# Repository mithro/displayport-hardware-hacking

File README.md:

View this project on [CADLAB.io](https://cadlab.io/project/2210). 

This repository contains schematics for working with DisplayPort.

Currently there are three sub-projects;

 * dp-aux-intercept - A board for connecting DisplayPort AUX signals to FPGA
   boards for interception and manipulation.

 * dp-to-pcie - An adapter board for allowing FPGA development boards with
   PCI-Express 4x interfaces to be instead used with DisplayPort.

 * dp-to-hsmc - An expansion board for the Altera HSMC standard supporting up
   to two DisplayPort sinks and two DisplayPort sources.

These works are released under the 
[Creative Commons Attribution-ShareAlike 4.0 International License (CC BY-SA 4.0)](http://creativecommons.org/licenses/by-sa/4.0/)

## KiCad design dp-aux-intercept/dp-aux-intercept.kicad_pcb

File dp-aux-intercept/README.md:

This schematic is design to allow FPGA development boards to intercept and
manipulate the auxiliary signals (plus hotplug and config signals) between a
display port source (such as a computer) and a display port sink (such as a
display). The high speed data lanes are connected directly between the source
and sink and not accessible.

The AUX signal is bi-directional, half duplex LVDS signal which operates at
~1.2 Megabit/s on older DisplayPort versions and ~720 Megabit/s in the later
specifications. It carries information device management and control data such
as EDID and DPMS standards. In theory it could also carry a USB signal.

# Board Manufacturing

 *  5mil (0.127mm) trace width
 *  5mil (0.127mm) trace clearance

 * 12 mil (0.3048mm) drill size
 *  6 mil (0.1524mm) annular ring
 * 24 mil (0.6096mm) via size (6mil+12mil+6mil)

 *  6 mil (0.1524) silkscreen width

This can be meet by;
 * [Hackvana by requesting the 5mil option](https://docs.google.com/document/d/1p6FH25ltGpzJQ5_8fbflDukqEKghiEcpuhJpngth2Is/edit)
 * [OHS Park's Four Layer Boards](http://docs.oshpark.com/services/)

# Board connectors
 
The board breaks out the AUX signals onto two Diligent PMOD compatible headers.
The JAUX jumpers select which PMOD header is currently in use.

## PAUX1 Mode

The first PMOD header labeled PAUX1 is designed to be used by devices which
support switching the direction of their I/O pins quickly enough. It maps both
AUX pairs and the HPD (hot plug) signal into a single PMOD connector. FPGAs
compatible with this are;

 * Spartan 6 when using the DISPLAY_PORT I/O standard (which only supports the
   1.2 Megabit/s mode).

 * Xilinx Series 7 FPGAs such as the Atrix, Zynq or Virtex-7 devices.

PAUX1 should be connected to the FPGA;

 * Pin 1 - AUX+ signal on computer side, configure 2.5V compatible
   bi-directional LVDS.
 * Pin 3 - AUX- signal on computer side, configure 2.5V compatible
   bi-directional LVDS.
 * Pin 5 is NC.
 * Pin 7 - HPD on computer side, configure 3.3V compatible LVCMOS33 output.

 * Pin 2 - AUX+ signal on display side, configure 2.5V compatible
   bi-directional LVDS.
 * Pin 4 - AUX- signal on display side, configure 2.5V compatible
   bi-directional LVDS.
 * Pin 6 is NC.
 * Pin 8 - HPD on display side, configure 3.3V compatible LVCMOS33 input.

 * Pin 9 and Pin 10 - 3.3V - VCC
 * Pin 11 and Pin 12 - GND

When using PAUX1 the board should be configured as follows;

 * All the JAUX jumpers are set to the "1" side (jumping Pin 1 and Pin 2
   together).

 * On PCFG1, Pins 5 and Pin 6 should **not be** connected.
   (**Dis**connecting the HPD signal from computer to display, allowing the
    FPGA to control the HPD signal.)

 * On J**C**CFG1, Pins 5 and Pin 6 should **be** connected.
   (Pulling the HPD signal on the **c**omputer side down.)

 * On J**D**CFG1, Pins 5 and Pin 6 should **be** connected.
   (Pulling the HPD signal on the **d**isplay side down.)

## PAUX2 Mode

The second PMOD header labeled PAUX2 is designed to be used by devices which
need to use two pairs of LVDS pins connected to each AUX lines. (When using
PAUX2 a second PMOD header the only way to receive the HPD is to use the PCFG1
header.) FPGAs compatible with this header are;

 * Spartan 6 when using the LVDS I/O standard.

To use PAUX2, you must always make sure the board has the following configured;

 * All the JAUX jumpers are set to the "2" side (jumping Pin 2 and Pin 3
   together).

PAUX2 should be connected to the FPGA in the following way;

 * Pin 1 - AUX+ signal on computer side, configure 2.5V compatible
   **output** LVDS.
 * Pin 3 - AUX- signal on computer side, configure 2.5V compatible
   **output** LVDS.

 * Pin 5 - AUX+ signal on computer side, configure 2.5V compatible
   **input** LVDS.
 * Pin 7 - AUX- signal on computer side, configure 2.5V compatible
   **input** LVDS.

 * Pin 2 - AUX+ signal on display side, configure 2.5V compatible
   **output** LVDS.
 * Pin 4 - AUX- signal on display side, configure 2.5V compatible
   **output** LVDS.

 * Pin 6 - AUX+ signal on display side, configure 2.5V compatible
   **input** LVDS.
 * Pin 8 - AUX- signal on display side, configure 2.5V compatible
   **input** LVDS.

 * Pin 9 and Pin 10 - 3.3V - VCC
 * Pin 11 and Pin 12 - GND

When using PAUX2 the board should be configured in one of two ways. 

If access to the HPD is **needed** follow the instructions for **using** the
PCFG1 expanded signals connector.

If access to the HPD is **not needed**;

 * On PCFG1, Pins 5 and Pin 6 should **be** connected. 
   (Connecting the HPD signal from computer to display.)

 * On J**C**CFG1, Pins 5 and Pin 6 should **not be** connected.
   (Leaving the HPD signal on the **c**omputer side floating.)

 * On J**D**CFG1, Pins 5 and Pin 6 should **not be** connected.
   (Leaving the HPD signal on the **d**isplay side floating.)

## PCFG1 - Expanded signals

The PCFG1 is also a PMOD compatible header but is found in male form to allow
it to also be used with jumpers. This header provides access to the CONFIG
lines (used with DP++ signaling) and alternative access to the HPD signal when
using PAUX2 mode.

#### Not using extended signals

When **not using** PCFG1, the board should be configured as follows;

 * On PCFG1;
   * Pin 1 and Pin 2 should **be** connected. 
     (Connecting CONFIG1 directly from the computer to the display.)

   * Pin 3 and Pin 4 should **be** connected.
     (Connecting CONFIG2 directly from the computer to the display.)

   * Pin 5 and Pin 6 should be configured as described in either PAUX1 or PAUX2
     section.

 * On J**C**CFG1,
   * Pins 1 and Pin 2 should **not be** connected.
     (Leaving the CONFIG1 signal on the **c**omputer side floating.)

   * Pins 3 and Pin 4 should **not be** connected.
     (Leaving the CONFIG2 signal on the **c**omputer side floating.)

   * Pin 5 and Pin 6 should be configured as described in either PAUX1 or PAUX2
     section.

 * On J**D**CFG1,
   * Pins 1 and Pin 2 should **not be** connected.
     (Leaving the CONFIG1 signal on the **d**isplay side floating.)

   * Pins 3 and Pin 4 should **not be** connected.
     (Leaving the CONFIG2 signal on the **d**isplay side floating.)

   * Pin 5 and Pin 7 should be configured as described in either PAUX1 or PAUX2
     section.

#### Using extended signals

PCFG1 should be connected to your FPGA.

 * Pin 1 - CONFIG1 on computer side, configure 3.3V compatible LVCMOS33
   ?input?.
 * Pin 3 - CONFIG2 on computer side, configure 3.3V compatible LVCMOS33
   ?input?.
 * Pin 5 - HPD on computer side, configure 3.3V compatible LVCMOS33 output.

 * Pin 2 - CONFIG1 on display side, configure 3.3V compatible LVCMOS33 ?input?.
 * Pin 4 - CONFIG2 on display side, configure 3.3V compatible LVCMOS33 ?input?.
 * Pin 6 - HPD on display side, configure 3.3V compatible LVCMOS33 input.

When **using** PCFG1, the board should be configured as follows;

 * On J**C**CFG1,
   * Pins 1 and Pin 2 should **be** connected.
     (Leaving the CONFIG1 signal on the **c**omputer side floating.)

   * Pins 3 and Pin 4 should **not be** connected.
     (Leaving the CONFIG2 signal on the **c**omputer side floating.)

   * Pin 4 and Pin 5 should be configured as described in either PAUX1 or PAUX2
     section.

 * On J**D**CFG1,
   * Pins 1 and Pin 2 should **not be** connected.
     (Leaving the CONFIG1 signal on the **d**isplay side floating.)

   * Pins 3 and Pin 4 should **not be** connected.
     (Leaving the CONFIG2 signal on the **d**isplay side floating.)

   * Pin 4 and Pin 5 should be configured as described in either PAUX1 or PAUX2
     section.

 * PCFG1 should be connected to the FPGA. Pins 5 and Pin 6 will provide the HPD
   signals.

 * On J**C**CFG1, Pins 5 and Pin 6 should **be** connected.
   (Pulling the HPD signal on the **c**omputer side down.)

 * On J**D**CFG1, Pins 5 and Pin 6 should **be** connected.
   (Pulling the HPD signal on the **d**isplay side down.)

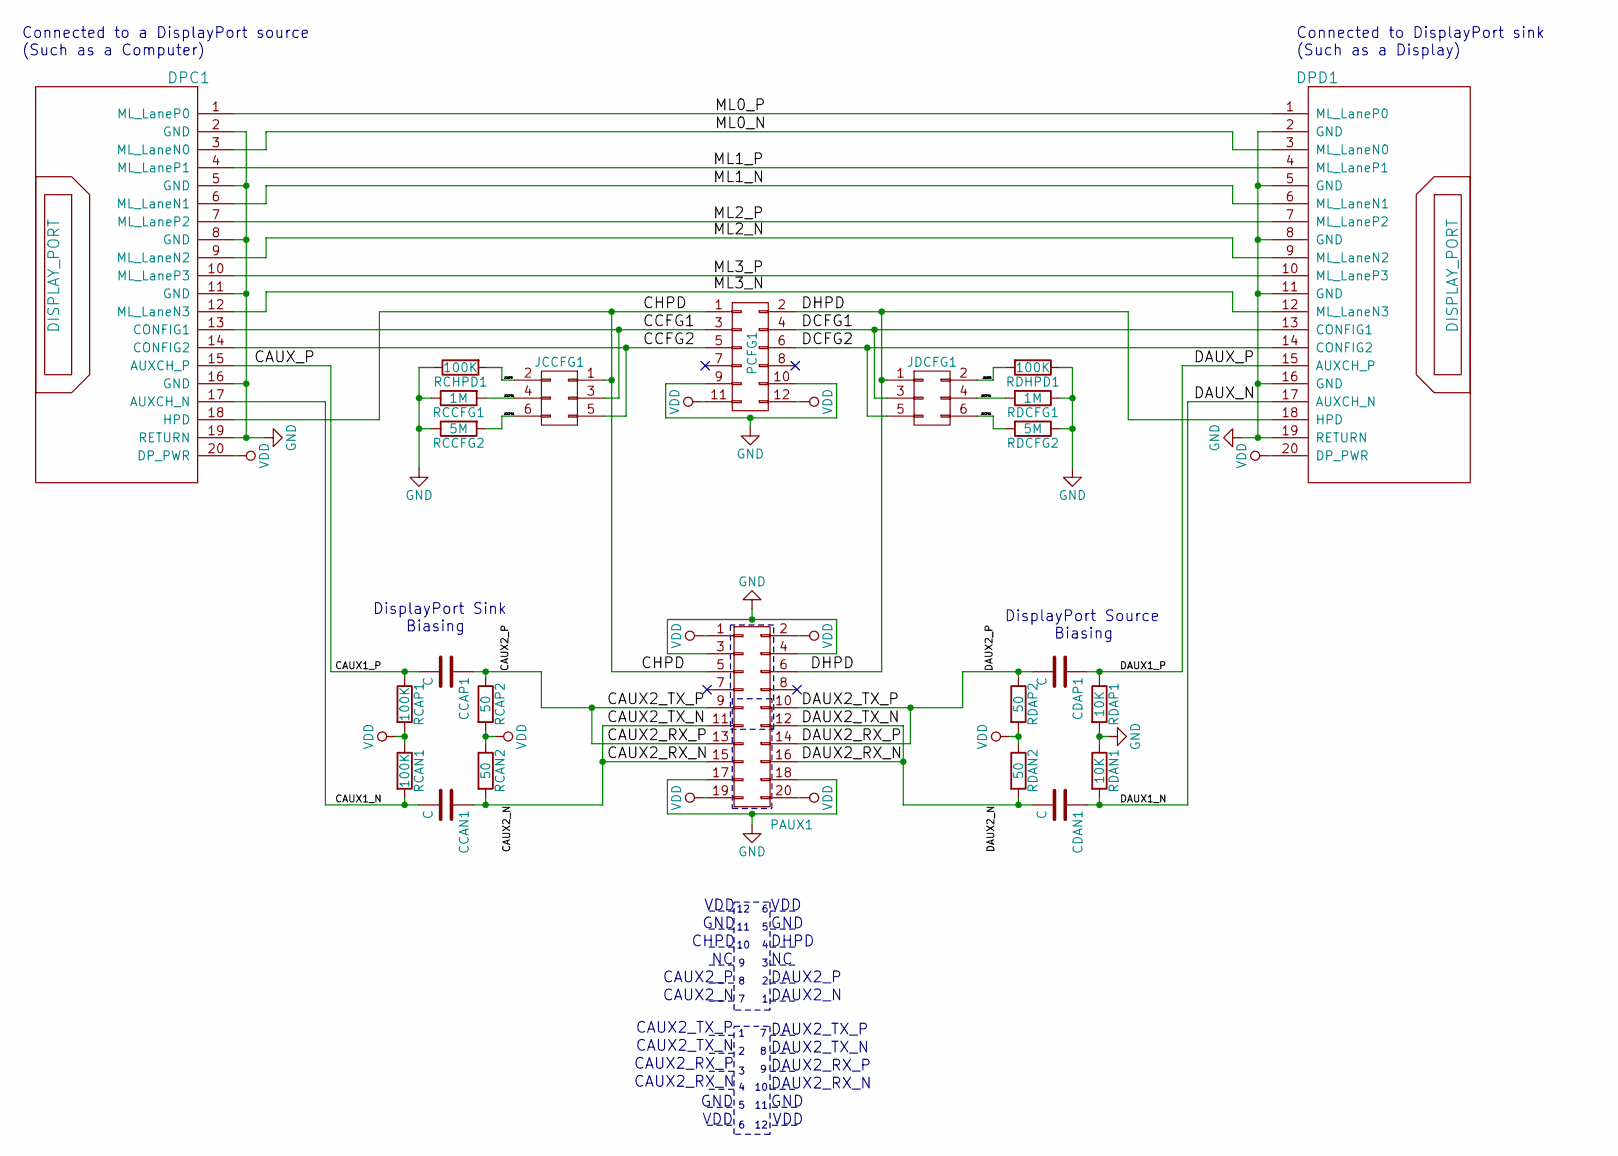
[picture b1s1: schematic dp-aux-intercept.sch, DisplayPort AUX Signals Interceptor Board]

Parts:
CCAN1: C; C_0805_HandSoldering
CCAP1: C; C_0805_HandSoldering
CDAN1: C; C_0805_HandSoldering
CDAP1: C; C_0805_HandSoldering
DPC1: DISPLAY_PORT; 2040210-1
DPD1: DISPLAY_PORT; 2040210-1
JCCFG1: CONN_02X03; Pin_Header_Straight_2x03
JDCFG1: CONN_02X03; Pin_Header_Straight_2x03
PAUX1: CONN_02X10; Socket_Strip_Angled_2x10
PCFG1: CONN_02X06; Pin_Header_Straight_2x06
RCAN1: 100K; R_0603_HandSoldering
RCAN2: 50; R_0603_HandSoldering
RCAP1: 100K; R_0603_HandSoldering
RCAP2: 50; R_0603_HandSoldering
RCCFG1: 1M; R_0603_HandSoldering
RCCFG2: 5M; R_0603_HandSoldering
RCHPD1: 100K; R_0603_HandSoldering
RDAN1: 10K; R_0603_HandSoldering
RDAN2: 50; R_0603_HandSoldering
RDAP1: 10K; R_0603_HandSoldering
RDAP2: 50; R_0603_HandSoldering
RDCFG1: 1M; R_0603_HandSoldering
RDCFG2: 5M; R_0603_HandSoldering
RDHPD1: 100K; R_0603_HandSoldering

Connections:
/CAUX1_N: CCAN1.2, DPC1.17 (AUXCH_N), RCAN1.2
/CAUX1_P: CCAP1.2, DPC1.15 (AUXCH_P), RCAP1.1
/CAUX2_N: CCAN1.1, PAUX1.11, PAUX1.15, RCAN2.2
/CAUX2_P: CCAP1.1, PAUX1.9, PAUX1.13, RCAP2.1
/CCFG1: DPC1.13 (CONFIG1), JCCFG1.3, PCFG1.3
/CCFG2: DPC1.14 (CONFIG2), JCCFG1.5, PCFG1.5
/CHPD: DPC1.18 (HPD), JCCFG1.1, PAUX1.5, PCFG1.1
/DAUX1_N: CDAN1.1, DPD1.17 (AUXCH_N), RDAN1.2
/DAUX1_P: CDAP1.1, DPD1.15 (AUXCH_P), RDAP1.1
/DAUX2_N: CDAN1.2, PAUX1.12, PAUX1.16, RDAN2.2
/DAUX2_P: CDAP1.2, PAUX1.10, PAUX1.14, RDAP2.1
/DCFG1: DPD1.13 (CONFIG1), JDCFG1.3, PCFG1.4
/DCFG2: DPD1.14 (CONFIG2), JDCFG1.5, PCFG1.6
/DHPD: DPD1.18 (HPD), JDCFG1.1, PAUX1.6, PCFG1.2
/JCCFG1: JCCFG1.4, RCCFG1.2
/JCCFG2: JCCFG1.6, RCCFG2.2
/JCHPD: JCCFG1.2, RCHPD1.2
/JDCFG1: JDCFG1.4, RDCFG1.2
/JDCFG2: JDCFG1.6, RDCFG2.2
/JDHPD: JDCFG1.2, RDHPD1.2
/ML0_N: DPC1.3 (ML_LaneN0), DPD1.3 (ML_LaneN0)
/ML0_P: DPC1.1 (ML_LaneP0), DPD1.1 (ML_LaneP0)
/ML1_N: DPC1.6 (ML_LaneN1), DPD1.6 (ML_LaneN1)
/ML1_P: DPC1.4 (ML_LaneP1), DPD1.4 (ML_LaneP1)
/ML2_N: DPC1.9 (ML_LaneN2), DPD1.9 (ML_LaneN2)
/ML2_P: DPC1.7 (ML_LaneP2), DPD1.7 (ML_LaneP2)
/ML3_N: DPC1.12 (ML_LaneN3), DPD1.12 (ML_LaneN3)
/ML3_P: DPC1.10 (ML_LaneP3), DPD1.10 (ML_LaneP3)
GND: DPC1.2 (GND), DPC1.5 (GND), DPC1.8 (GND), DPC1.11 (GND), DPC1.16 (GND), DPC1.19 (RETURN), DPD1.2 (GND), DPD1.5 (GND), DPD1.8 (GND), DPD1.11 (GND), DPD1.16 (GND), DPD1.19 (RETURN), PAUX1.3, PAUX1.4, PAUX1.17, PAUX1.18, PCFG1.9, PCFG1.10, RCCFG1.1, RCCFG2.1, RCHPD1.1, RDAN1.1, RDAP1.2, RDCFG1.1, RDCFG2.1, RDHPD1.1
VDD: DPC1.20 (DP_PWR), DPD1.20 (DP_PWR), PAUX1.1, PAUX1.2, PAUX1.19, PAUX1.20, PCFG1.11, PCFG1.12, RCAN1.1, RCAN2.1, RCAP1.2, RCAP2.2, RDAN2.1, RDAP2.2

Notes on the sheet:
DisplayPort Sink Biasing
Connected to a DisplayPort source (Such as a Computer)
Connected to DisplayPort sink (Such as a Display)
DisplayPort Source Biasing
VDD
GND
CHPD
DHPD
DAUX2_P
DAUX2_N
CAUX2_P
CAUX2_N
DAUX2_TX_P
DAUX2_TX_N
CAUX2_TX_P
CAUX2_TX_N
DAUX2_RX_P
DAUX2_RX_N
CAUX2_RX_P
CAUX2_RX_N

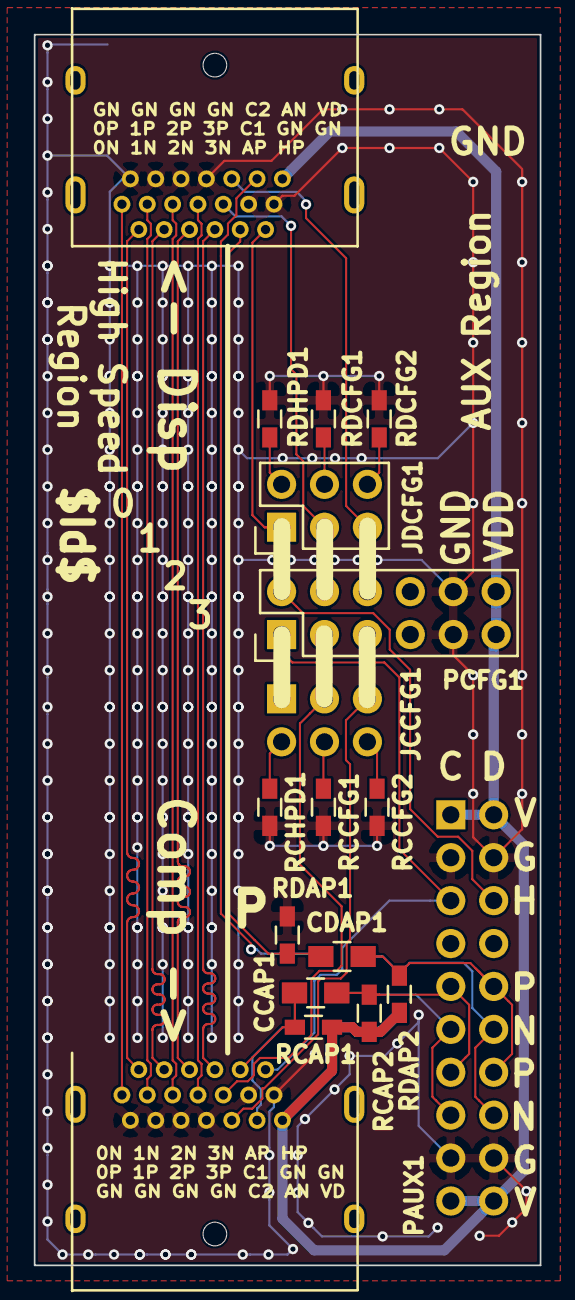
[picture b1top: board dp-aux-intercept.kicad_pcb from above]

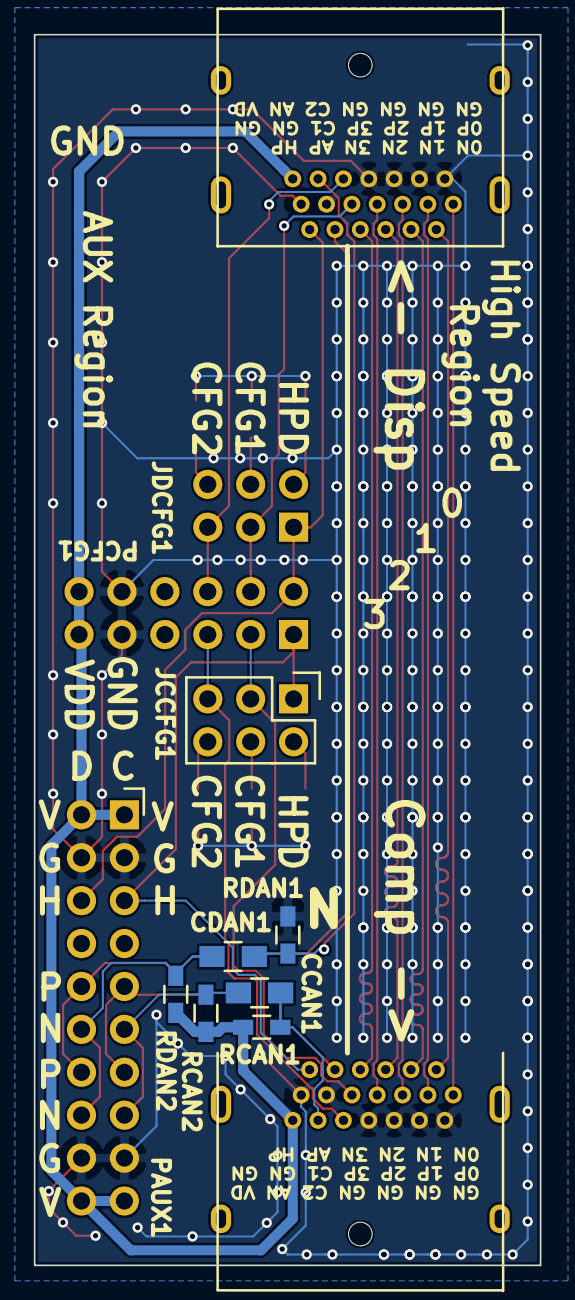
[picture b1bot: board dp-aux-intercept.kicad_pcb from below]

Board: 4 copper layers, 29.9 x 72.9 mm, 24 parts (9 on the bottom side), 30 nets.

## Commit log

2015-06-13 Adding DisplayPort and PCIe connectors.
2015-06-13 Initial empty schematic and project.
2015-06-13 Adding initial schematic for the interceptor.
2015-06-13 Adding initial README and license file.
2015-06-13 Adding .gitignore file.
2015-06-13 Updates to the dp-to-pcie schematic.
2015-06-13 Updating the comments in the schematic.
2015-06-13 Initial empty schematic.
2015-06-13 Initial scatter.
2015-06-13 More backup files..
2015-06-13 Work on the PCB.
2015-06-13 Rename the display port part to match component name.
2015-06-13 Adding through hole DisplayPort component.
2015-06-13 Update library information.
2015-06-13 Adding newline to README.md
2015-06-13 Adding a README file for the dp-to-pcie schematic.
2015-06-13 Adding a README for the HSMC to DisplayPort project.
2015-06-13 Adding schematic description.
2015-06-13 Adding more descriptions.
2015-06-15 Adding some extra info about the HSMC stuff.
2015-06-15 Add DisplayPort footprint.
2015-06-15 Adding part from @brightcloudy
2015-06-15 Changing to using the through-hole DisplayPort connectors.
2015-06-15 Importing the updated netlist.
2015-06-15 Changing the PAUX1 and PAUX2 to be right angle connectors.
2015-06-15 Assigning footprints to AUX select headers.
2015-06-15 Temp commit.
2015-06-15 Adding silkscreen to both sides.
2015-06-15 Lots of updates to the PCB.
2015-06-16 Alternative method of two PMOD styles.
2015-06-16 Enough routing for tonight.
2015-06-17 Information about the Xilinx KC705 board.
2015-06-17 Add QTH-0909-01-L-D-A footprint.
2015-06-17 Added schematic part for QTH-090-01-L-D-A.
2015-06-19 Start of the dp-to-hsmc stuff.
2015-06-19 Adding the HSMC part from @brightcloudy
2015-06-19 Updated QTH-090-01-L-D-A pinout to comply with HSMC pinout. Created HSMC-SE.lib for HSMC Standard Single-Ended pin assignment.
2015-06-19 Add HSMC Standard Differential Configuration schematic part.
2015-06-19 Add mounting holes in the QTH-090-01-L-D-A footprint.
2015-06-28 PCB routing temp commit.
2015-06-28 Adding a .keepme file.
2015-06-28 Moving around in preparation for merging.
2015-06-28 Adding pin information CSV files.
2015-06-28 Adding link to spreadsheet with further info.
2015-06-28 Small fixes.
2015-06-28 Reordering headers to make routing easier.
2015-06-28 More temp commit.
2016-06-24 Finishing connecting the traces.
2016-06-24 Converting mm to mil.
    * 0.125mm -> 5mil (0.1270mm)
    * 0.150mm -> 6mil (0.1524mm)
2016-06-24 Converting to 5mil/5mil + Documenting the DRC requested.
2016-06-24 Small connectivity fix.
2016-06-24 Fixing the vias
2016-06-24 Adding ground plane and tie vias
2016-06-24 Lots of work.
    * Fixing the GND tie vias.
    * Working on the silkscreen.
2016-06-24 Working on the silk screen.
2016-07-03 Fixing the hackvana link.
2016-08-01 Improving the silk screen.
2016-08-01 Better alignment of Id value.
2016-08-01 Going to have multi gerber's eventually.
2016-08-01 Adding a script to release the gerbers.
2016-08-01 Making the version text smaller.
2016-08-01 Creating gerbers v0.0-66-g0a24827 for dp-aux-intercept
2016-08-03 Fixing the release script.
2016-08-23 Adding some HSMC info.
2019-10-17 Backlink to CADLAB.io has been added.

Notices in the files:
README.md:
Creative Commons License - CC-BY-SA
dp-aux-intercept/dp-aux-intercept.sch:
License: CC-BY-SA 4.0 International
